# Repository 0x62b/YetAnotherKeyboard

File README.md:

# YetAnotherKeyboard
This is an 65% mechanical keyboard with hot-swappable MX style switches. The design is based on a nice!nano microcontroller and a nice!view display.
It also supports wireless operation with a standard lithium polymer battery. The nano also supports a USB connection.

## Repo structure
- CAD files including the individual parts and full assembly can be found in `cad/`
- The KiCad PCB design files can be found in `PCB/`
- Production gerbers can be found in `PCB/production`
- Firmware can be found in `firmware/`

## BOM
Total cost: 55.39 USD\
Parts can all be sourced from AliExpress.

## PCB
Parameters:
* 2 layer
* Material: FR-4
* Either HASL (leaded is much cheaper)
* White solder mask

Dimensions: 98.21mm*329.75mm\
PCB cost: 17 USD\
Shipping cost: 12.83 USD\
Total cost: 29.83 USD

## Case
Material: PLA, PETG, anything is fine really\
Nozzle: 0.4mm/0.6mm/0.8mm\
The case is far too big to fit on a standard 256mm^3 bed. If you want to replicate this build (for some reason) you may need to split the case. However I have access to a Prusa XL so I will use that.

## Firmware
ZMK, firmware is located in a submodule, https://github.com/0x62b/YetAnotherKeyboard-config

## Cost
Parts: 55.39 USD\
PCB: 29.83 USD\
Grand total: 85.22 USD (approx because of conversion rates)

## Images

There's probably a more efficient way to do matrix but...

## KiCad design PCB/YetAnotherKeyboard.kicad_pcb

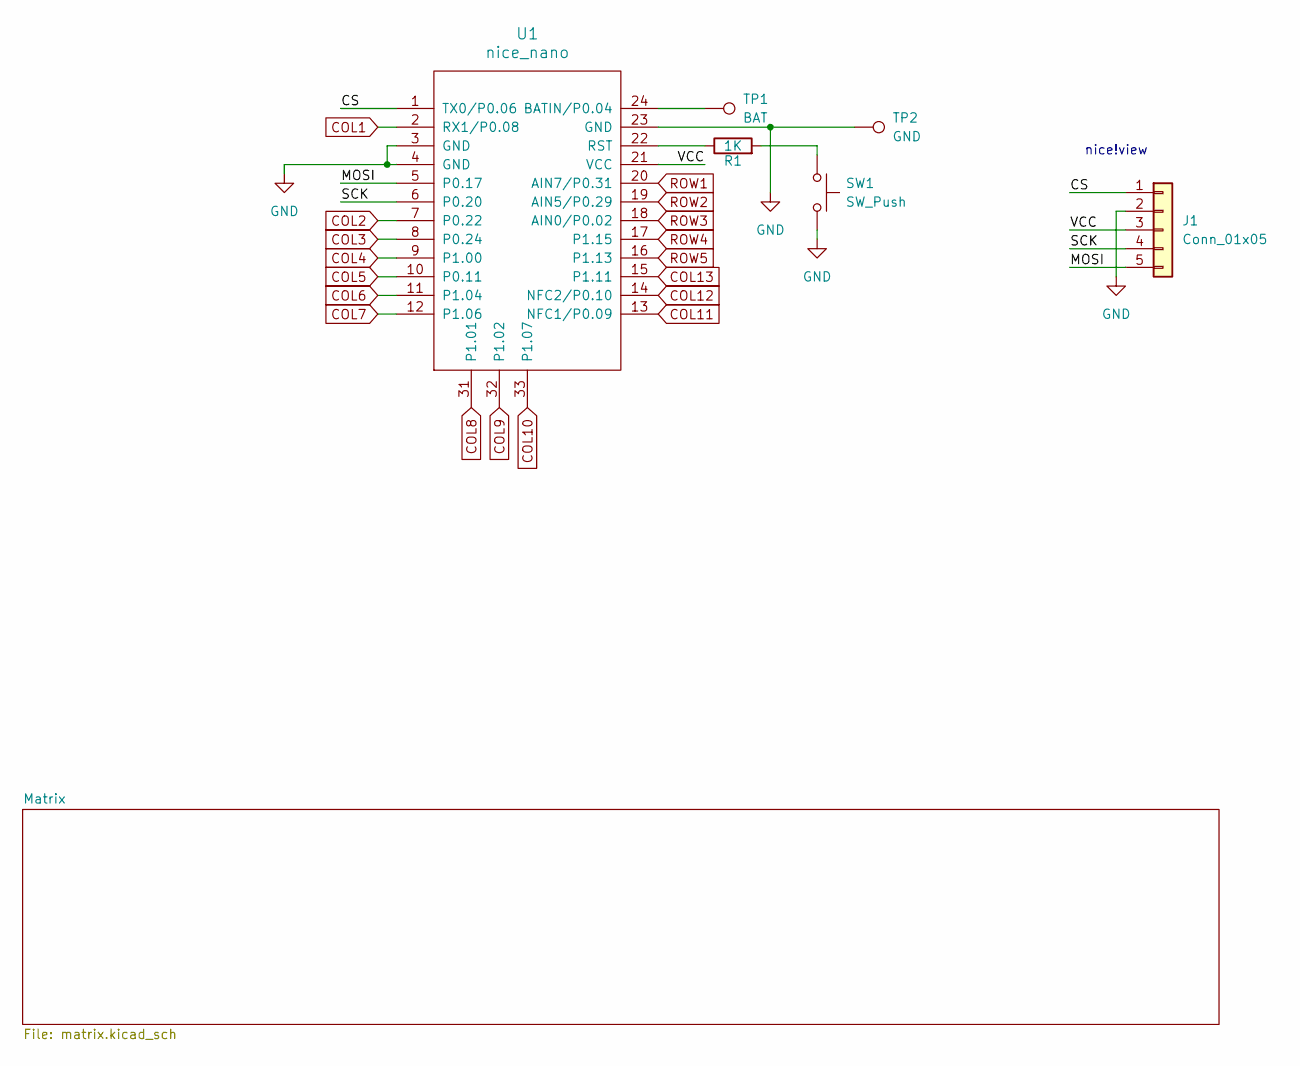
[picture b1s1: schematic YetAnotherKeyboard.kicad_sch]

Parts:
J1: Conn_01x05; PinHeader_1x05_P2.54mm_Vertical
R1: 1K; R_0402_1005Metric
SW1: SW_Push; SW_Push_SPST_NO_Alps_SKRK
TP1: BAT; TestPoint_Pad_D2.0mm
TP2: GND; TestPoint_Pad_D2.0mm
U1: nice_nano

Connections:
/CS: J1.1, U1.1 (TX0/P0.06)
/MOSI: J1.5, U1.5 (P0.17)
/SCK: J1.4, U1.6 (P0.20)
/VCC: J1.3, U1.21 (VCC)
COL1: U1.2 (RX1/P0.08); also elsewhere on the board
COL2: U1.7 (P0.22); also elsewhere on the board
COL3: U1.8 (P0.24); also elsewhere on the board
COL4: U1.9 (P1.00); also elsewhere on the board
COL5: U1.10 (P0.11); also elsewhere on the board
COL6: U1.11 (P1.04); also elsewhere on the board
COL7: U1.12 (P1.06); also elsewhere on the board
COL8: U1.31 (P1.01); also elsewhere on the board
COL9: U1.32 (P1.02); also elsewhere on the board
COL10: U1.33 (P1.07); also elsewhere on the board
COL11: U1.13 (NFC1/P0.09); also elsewhere on the board
COL12: U1.14 (NFC2/P0.10); also elsewhere on the board
COL13: U1.15 (P1.11); also elsewhere on the board
GND: J1.2, SW1.2, TP2.1 (1_1), U1.3 (GND), U1.4 (GND), U1.23 (GND)
unnamed: R1.2, SW1.1
unnamed: TP1.1 (1_1), U1.24 (BATIN/P0.04)
unnamed: R1.1, U1.22 (RST)
ROW1: U1.20 (AIN7/P0.31); also elsewhere on the board
ROW2: U1.19 (AIN5/P0.29); also elsewhere on the board
ROW3: U1.18 (AIN0/P0.02); also elsewhere on the board
ROW4: U1.17 (P1.15); also elsewhere on the board
ROW5: U1.16 (P1.13); also elsewhere on the board

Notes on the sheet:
nice!view

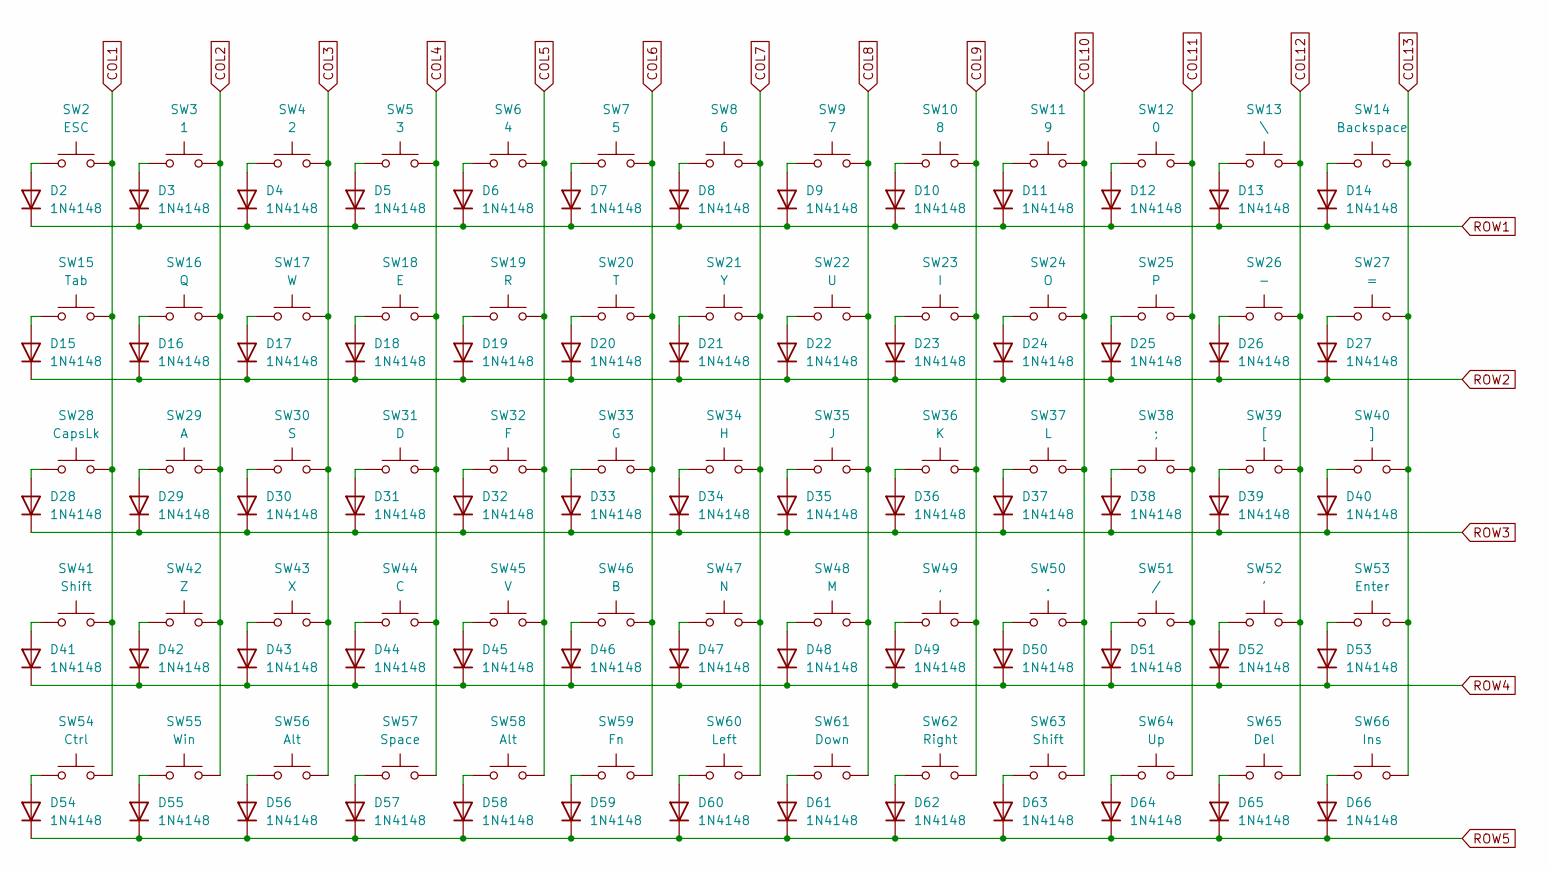
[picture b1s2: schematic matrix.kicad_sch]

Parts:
D2, D3, D4, D5, D6, D7, D8, D9, D10, D11, D12, D13, D14, D15, D16, D17, D18, D19, D20, D21, D22, D23, D24, D25, D26, D27, D28, D29, D30, D31, D32, D33, D34, D35, D36, D37, D38, D39, D40, D41, D42, D43, D44, D45, D46, D47, D48, D49, D50, D51, D52, D53, D54, D55, D56, D57, D58, D59, D60, D61, D62, D63, D64, D65, D66: 1N4148; D_SOD-123
SW2: ESC; MX-Hotswap-1U
SW3: 1; MX-Hotswap-1U
SW4: 2; MX-Hotswap-1U
SW5: 3; MX-Hotswap-1U
SW6: 4; MX-Hotswap-1U
SW7: 5; MX-Hotswap-1U
SW8: 6; MX-Hotswap-1U
SW9: 7; MX-Hotswap-1U
SW10: 8; MX-Hotswap-1U
SW11: 9; MX-Hotswap-1U
SW12: 0; MX-Hotswap-1U
SW13: \; MX-Hotswap-1.5U
SW14: Backspace; MX-Hotswap-2U
SW15: Tab; MX-Hotswap-1.5U
SW16: Q; MX-Hotswap-1U
SW17: W; MX-Hotswap-1U
SW18: E; MX-Hotswap-1U
SW19: R; MX-Hotswap-1U
SW20: T; MX-Hotswap-1U
SW21: Y; MX-Hotswap-1U
SW22: U; MX-Hotswap-1U
SW23: I; MX-Hotswap-1U
SW24: O; MX-Hotswap-1U
SW25: P; MX-Hotswap-1U
SW26: -; MX-Hotswap-1U
SW27: =; MX-Hotswap-1U
SW28: CapsLk; MX-Hotswap-1.75U
SW29: A; MX-Hotswap-1U
SW30: S; MX-Hotswap-1U
SW31: D; MX-Hotswap-1U
SW32: F; MX-Hotswap-1U
SW33: G; MX-Hotswap-1U
SW34: H; MX-Hotswap-1U
SW35: J; MX-Hotswap-1U
SW36: K; MX-Hotswap-1U
SW37: L; MX-Hotswap-1U
SW38: ;; MX-Hotswap-1U
SW39: [; MX-Hotswap-1U
SW40: ]; MX-Hotswap-1U
SW41: Shift; MX-Hotswap-2.25U
SW42: Z; MX-Hotswap-1U
SW43: X; MX-Hotswap-1U
SW44: C; MX-Hotswap-1U
SW45: V; MX-Hotswap-1U
SW46: B; MX-Hotswap-1U
SW47: N; MX-Hotswap-1U
SW48: M; MX-Hotswap-1U
SW49: ,; MX-Hotswap-1U
SW50: .; MX-Hotswap-1U
SW51: /; MX-Hotswap-1U
SW52: '; MX-Hotswap-1U
SW53: Enter; MX-Hotswap-2.25U
SW54: Ctrl; MX-Hotswap-1.25U
SW55: Win; MX-Hotswap-1.25U
SW56, SW58: Alt; MX-Hotswap-1.25U
SW57: Space; MX-Hotswap-6.25U
SW59: Fn; MX-Hotswap-1.25U
SW60: Left; MX-Hotswap-1U
SW61: Down; MX-Hotswap-1U
SW62: Right; MX-Hotswap-1U
SW63: Shift; MX-Hotswap-1.75U
SW64: Up; MX-Hotswap-1U
SW65: Del; MX-Hotswap-1U
SW66: Ins; MX-Hotswap-1U

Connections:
COL1: SW2.2, SW15.2, SW28.2, SW41.2, SW54.2; also elsewhere on the board
COL2: SW3.2, SW16.2, SW29.2, SW42.2, SW55.2; also elsewhere on the board
COL3: SW4.2, SW17.2, SW30.2, SW43.2, SW56.2; also elsewhere on the board
COL4: SW5.2, SW18.2, SW31.2, SW44.2, SW57.2; also elsewhere on the board
COL5: SW6.2, SW19.2, SW32.2, SW45.2, SW58.2; also elsewhere on the board
COL6: SW7.2, SW20.2, SW33.2, SW46.2, SW59.2; also elsewhere on the board
COL7: SW8.2, SW21.2, SW34.2, SW47.2, SW60.2; also elsewhere on the board
COL8: SW9.2, SW22.2, SW35.2, SW48.2, SW61.2; also elsewhere on the board
COL9: SW10.2, SW23.2, SW36.2, SW49.2, SW62.2; also elsewhere on the board
COL10: SW11.2, SW24.2, SW37.2, SW50.2, SW63.2; also elsewhere on the board
COL11: SW12.2, SW25.2, SW38.2, SW51.2, SW64.2; also elsewhere on the board
COL12: SW13.2, SW26.2, SW39.2, SW52.2, SW65.2; also elsewhere on the board
COL13: SW14.2, SW27.2, SW40.2, SW53.2, SW66.2; also elsewhere on the board
unnamed: D2.2 (A), SW2.1
unnamed: D3.2 (A), SW3.1
unnamed: D4.2 (A), SW4.1
unnamed: D5.2 (A), SW5.1
unnamed: D6.2 (A), SW6.1
unnamed: D7.2 (A), SW7.1
unnamed: D8.2 (A), SW8.1
unnamed: D9.2 (A), SW9.1
unnamed: D10.2 (A), SW10.1
unnamed: D11.2 (A), SW11.1
unnamed: D12.2 (A), SW12.1
unnamed: D13.2 (A), SW13.1
unnamed: D14.2 (A), SW14.1
unnamed: D15.2 (A), SW15.1
unnamed: D16.2 (A), SW16.1
unnamed: D17.2 (A), SW17.1
unnamed: D18.2 (A), SW18.1
unnamed: D19.2 (A), SW19.1
unnamed: D20.2 (A), SW20.1
unnamed: D21.2 (A), SW21.1
unnamed: D22.2 (A), SW22.1
unnamed: D23.2 (A), SW23.1
unnamed: D24.2 (A), SW24.1
unnamed: D25.2 (A), SW25.1
unnamed: D26.2 (A), SW26.1
unnamed: D27.2 (A), SW27.1
unnamed: D28.2 (A), SW28.1
unnamed: D29.2 (A), SW29.1
unnamed: D30.2 (A), SW30.1
unnamed: D31.2 (A), SW31.1
unnamed: D32.2 (A), SW32.1
unnamed: D33.2 (A), SW33.1
unnamed: D34.2 (A), SW34.1
unnamed: D35.2 (A), SW35.1
unnamed: D36.2 (A), SW36.1
unnamed: D37.2 (A), SW37.1
unnamed: D38.2 (A), SW38.1
unnamed: D39.2 (A), SW39.1
unnamed: D40.2 (A), SW40.1
unnamed: D41.2 (A), SW41.1
unnamed: D42.2 (A), SW42.1
unnamed: D43.2 (A), SW43.1
unnamed: D44.2 (A), SW44.1
unnamed: D45.2 (A), SW45.1
unnamed: D46.2 (A), SW46.1
unnamed: D47.2 (A), SW47.1
unnamed: D48.2 (A), SW48.1
unnamed: D49.2 (A), SW49.1
unnamed: D50.2 (A), SW50.1
unnamed: D51.2 (A), SW51.1
unnamed: D52.2 (A), SW52.1
unnamed: D53.2 (A), SW53.1
unnamed: D54.2 (A), SW54.1
unnamed: D55.2 (A), SW55.1
unnamed: D56.2 (A), SW56.1
unnamed: D57.2 (A), SW57.1
unnamed: D58.2 (A), SW58.1
unnamed: D59.2 (A), SW59.1
unnamed: D60.2 (A), SW60.1
unnamed: D61.2 (A), SW61.1
unnamed: D62.2 (A), SW62.1
unnamed: D63.2 (A), SW63.1
unnamed: D64.2 (A), SW64.1
unnamed: D65.2 (A), SW65.1
unnamed: D66.2 (A), SW66.1
ROW1: D2.1 (K), D3.1 (K), D4.1 (K), D5.1 (K), D6.1 (K), D7.1 (K), D8.1 (K), D9.1 (K), D10.1 (K), D11.1 (K), D12.1 (K), D13.1 (K), D14.1 (K); also elsewhere on the board
ROW2: D15.1 (K), D16.1 (K), D17.1 (K), D18.1 (K), D19.1 (K), D20.1 (K), D21.1 (K), D22.1 (K), D23.1 (K), D24.1 (K), D25.1 (K), D26.1 (K), D27.1 (K); also elsewhere on the board
ROW3: D28.1 (K), D29.1 (K), D30.1 (K), D31.1 (K), D32.1 (K), D33.1 (K), D34.1 (K), D35.1 (K), D36.1 (K), D37.1 (K), D38.1 (K), D39.1 (K), D40.1 (K); also elsewhere on the board
ROW4: D41.1 (K), D42.1 (K), D43.1 (K), D44.1 (K), D45.1 (K), D46.1 (K), D47.1 (K), D48.1 (K), D49.1 (K), D50.1 (K), D51.1 (K), D52.1 (K), D53.1 (K); also elsewhere on the board
ROW5: D54.1 (K), D55.1 (K), D56.1 (K), D57.1 (K), D58.1 (K), D59.1 (K), D60.1 (K), D61.1 (K), D62.1 (K), D63.1 (K), D64.1 (K), D65.1 (K), D66.1 (K); also elsewhere on the board

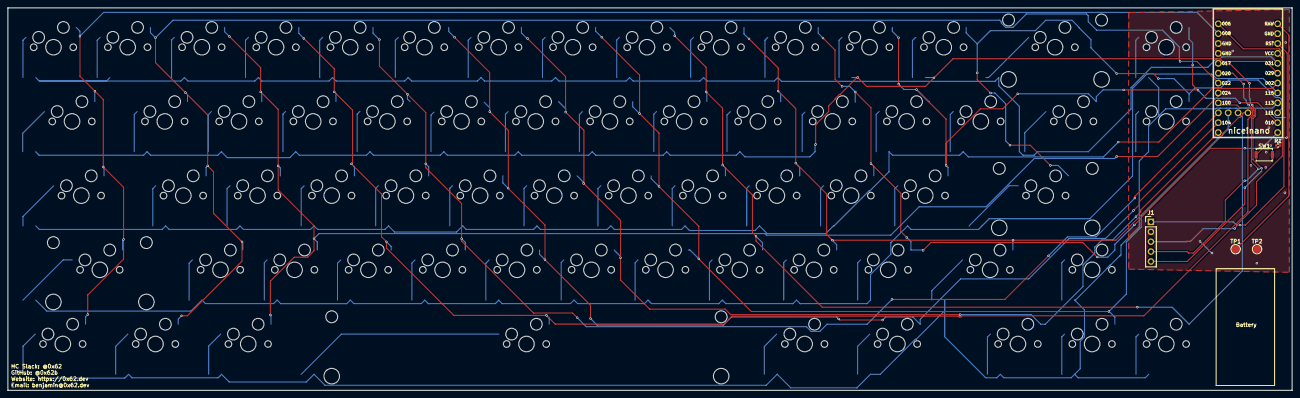
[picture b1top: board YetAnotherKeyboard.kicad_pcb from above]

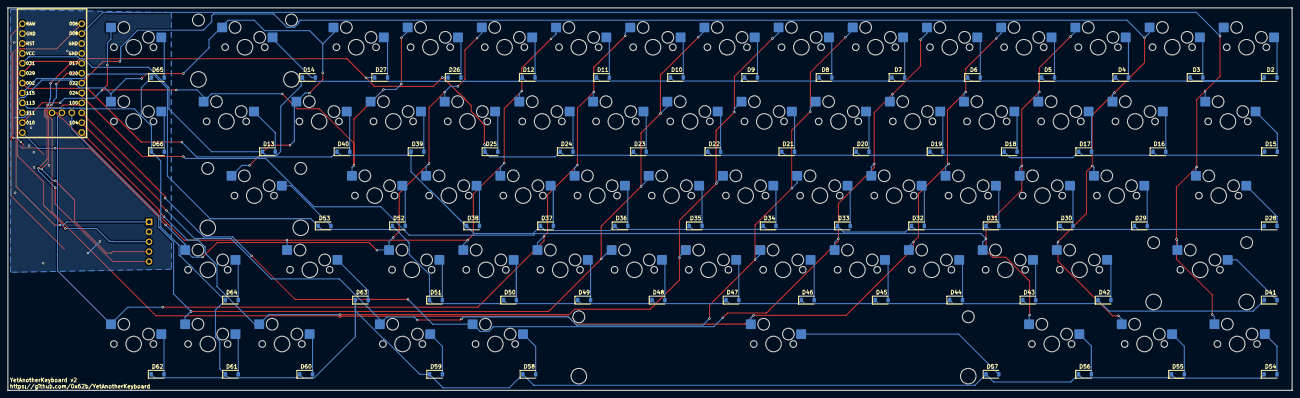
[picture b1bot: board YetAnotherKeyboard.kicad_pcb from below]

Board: 2 copper layers, 329.7 x 98.2 mm, 136 parts (130 on the bottom side), 91 nets.

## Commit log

2026-04-13 rev 1.1
2026-04-13 silkscreens
2026-04-14 production files, repo structure
2026-04-15 add dxf plate template
2026-04-15 fix footprints/adjust bom
2026-04-15 idt you CAN get a .4 resistor lmao
2026-04-15 add layout
2026-04-15 board + case files
2026-04-15 update bom to reflect actual prices
2026-04-15 add keycaps to bom
2026-04-15 add stabs to bom
2026-04-15 make the bom more complete :sparkles:
2026-04-15 note repo structure
2026-04-16 change schema to nice! compenents
2026-04-20 65% pcb
2026-04-20 new production files
2026-04-20 update bom for new pcb
2026-04-20 65% layout plate files
2026-04-21 case stl files
2026-04-21 add lockfiles to gitignore
2026-05-02 3d models
2026-05-02 board render
